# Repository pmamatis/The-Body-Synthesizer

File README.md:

Welcome to our lovely project. THE BODY-SYNTHESIZER. This is an educational project, which has been the topic of a course in digital signal processing and electronics at the Technical University Berlin, and is for non-commercial use only. The main goal of the project was to realize a digital audio-synthesizer, which can be controlled by various analog sensors. In case you wanna have a quick overview about the functionality, you can access the following YouTube-link: https://www.youtube.com/watch?v=VzIIO2eS0HQ&t=1586s

By: <br>
Maximillian Lehmer <br> Marc Bielen <br> Paul Mamatis

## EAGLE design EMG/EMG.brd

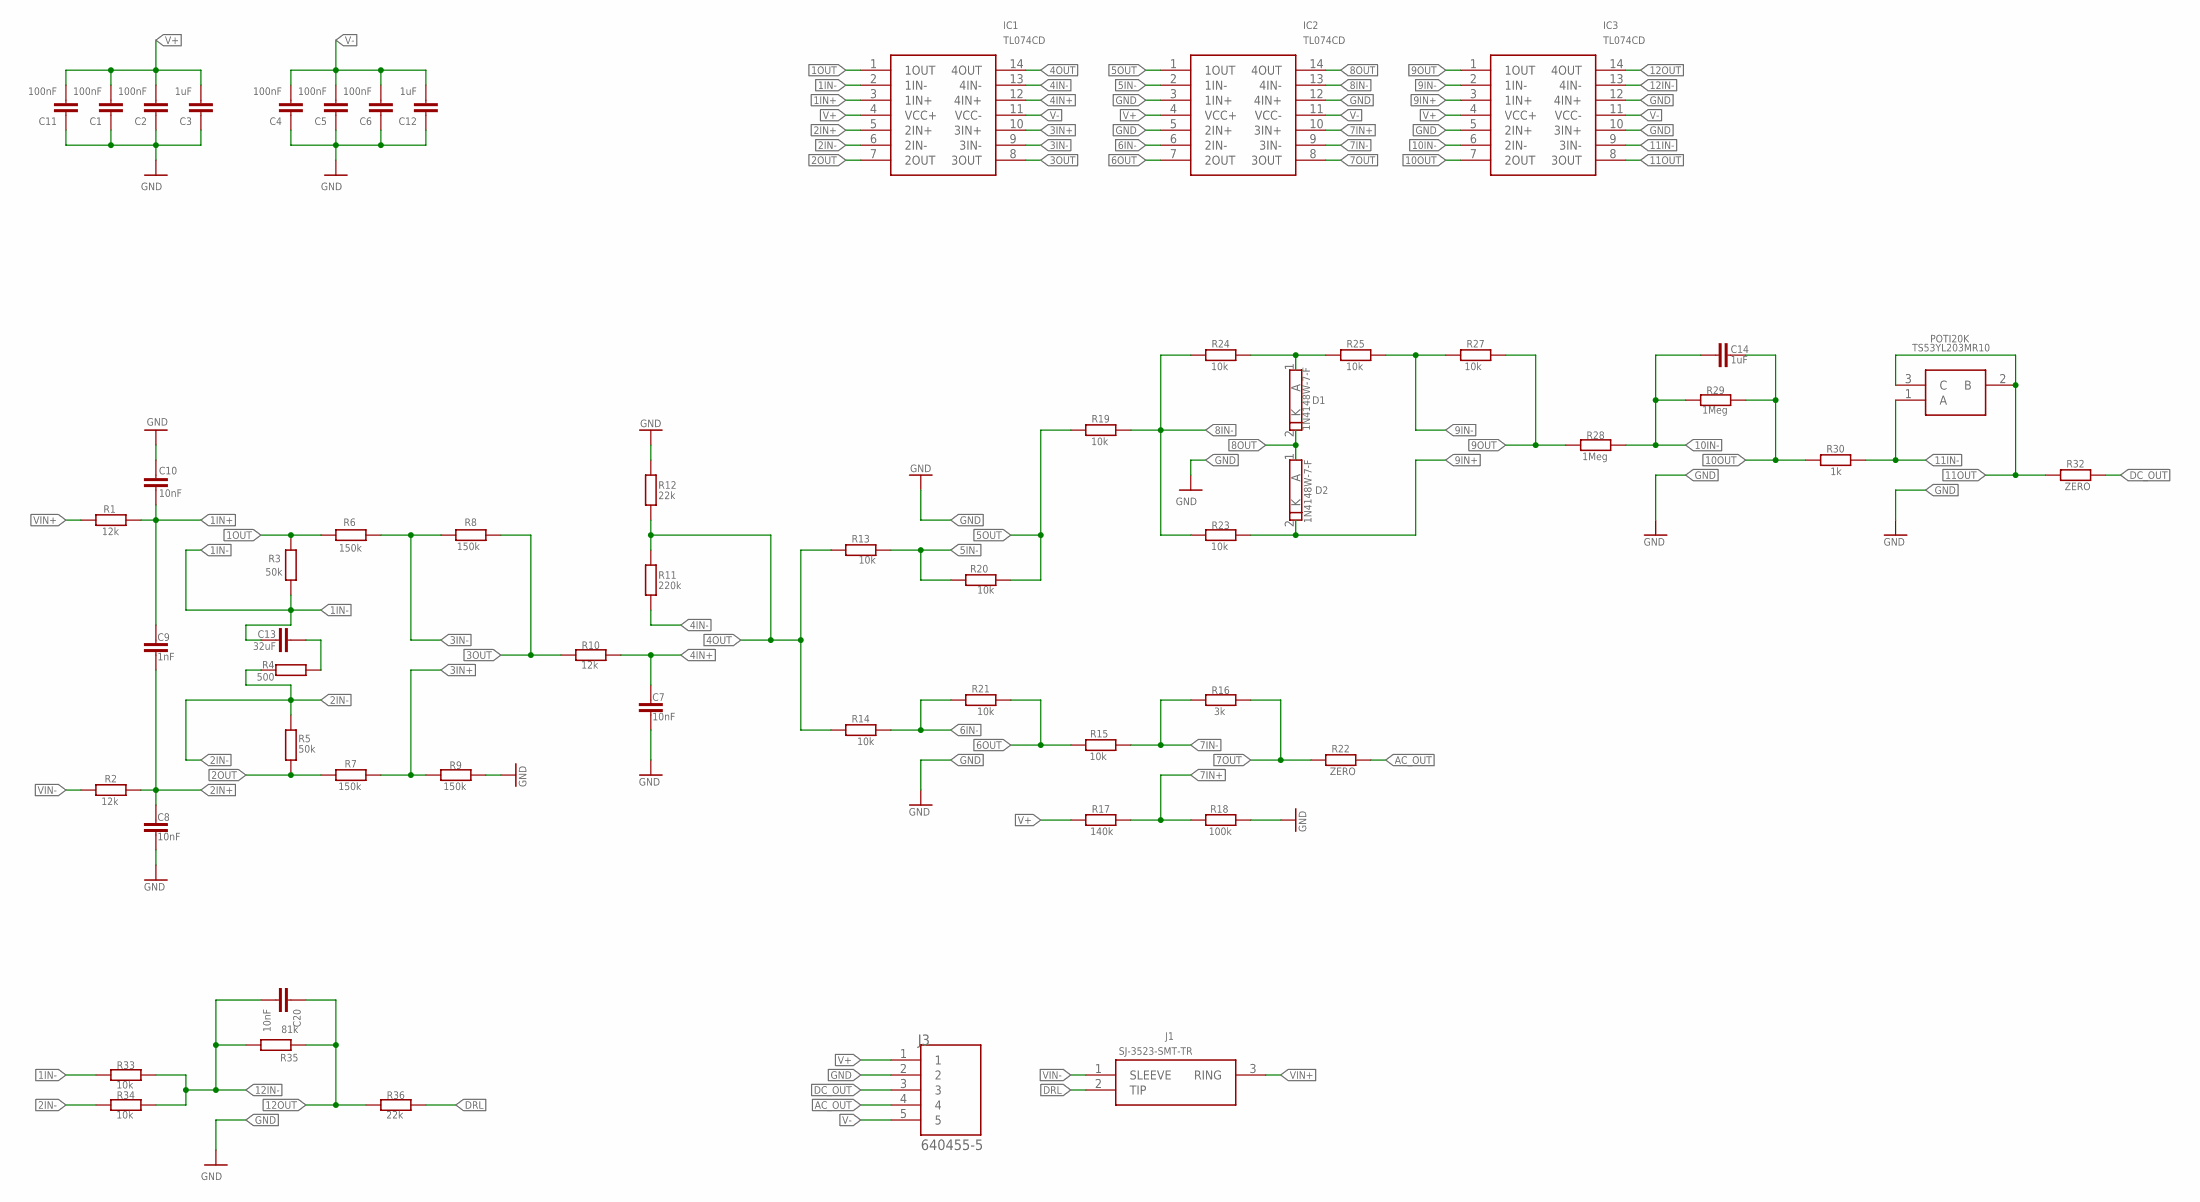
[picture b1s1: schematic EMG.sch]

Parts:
C1, C2, C4, C5, C6, C11: 100nF; C0603
C3, C12, C14: 1uF; C0603
C7, C8, C10, C20: 10nF; C0603
C9: 1nF; C0603
C13: 32uF; C0603
D1, D2: 1N4148W-7-F; SOD3716X115N
IC1, IC2, IC3: TL074CD; SOIC127P600X175-14N
J1: SJ-3523-SMT-TR; SJ3523SMTTR
J3: 640455-5; TE_640455-5
POTI20K: TS53YL203MR10
R1, R2, R10: 12k; R0603
R3, R5: 50k; R0603
R4: 500; R0603
R6, R7, R8, R9: 150k; R0603
R11: 220k; R0603
R12, R36: 22k; R0603
R13, R14, R15, R19, R20, R21, R23, R24, R25, R27, R33, R34: 10k; R0603
R16: 3k; R0603
R17: 140k; R0603
R18: 100k; R0603
R22, R32: ZERO; R0603
R28, R29: 1Meg; R0603
R30: 1k; R0603
R35: 81k; R0603

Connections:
1IN+: C9.1, C10.1, IC1.3 (1IN+), R1.2
1IN-: C13.1, IC1.2 (1IN-), R3.2, R33.2
1OUT: IC1.1 (1OUT), R3.1, R6.1
2IN+: C8.2, C9.2, IC1.5 (2IN+), R2.1
2IN-: IC1.6 (2IN-), R4.2, R5.1, R34.2
2OUT: IC1.7 (2OUT), R5.2, R7.2
3IN+: IC1.10 (3IN+), R7.1, R9.2
3IN-: IC1.9 (3IN-), R6.2, R8.2
3OUT: IC1.8 (3OUT), R8.1, R10.2
4IN+: C7.2, IC1.12 (4IN+), R10.1
4IN-: IC1.13 (4IN-), R11.2
4OUT: IC1.14 (4OUT), R11.1, R12.2, R13.2, R14.2
5IN-: IC2.2 (1IN-), R13.1, R20.2
5OUT: IC2.1 (1OUT), R19.2, R20.1
6IN-: IC2.6 (2IN-), R14.1, R21.2
6OUT: IC2.7 (2OUT), R15.2, R21.1
7IN+: IC2.10 (3IN+), R17.2, R18.1
7IN-: IC2.9 (3IN-), R15.1, R16.2
7OUT: IC2.8 (3OUT), R16.1, R22.2
8IN-: IC2.13 (4IN-), R19.1, R23.2, R24.2
8OUT: D1.2 (K), D2.1 (A), IC2.14 (4OUT)
9IN+: D2.2 (K), IC3.3 (1IN+), R23.1
9IN-: IC3.2 (1IN-), R25.1, R27.2
9OUT: IC3.1 (1OUT), R27.1, R28.2
10IN-: C14.1, IC3.6 (2IN-), R28.1, R29.2
10OUT: C14.2, IC3.7 (2OUT), R29.1, R30.2
11IN-: IC3.9 (3IN-), POTI20K.1 (A), R30.1
11OUT: IC3.8 (3OUT), POTI20K.2 (B), POTI20K.3 (C), R32.2
12IN-: C20.2, IC3.13 (4IN-), R33.1, R34.1, R35.2
12OUT: C20.1, IC3.14 (4OUT), R35.1, R36.2
AC_OUT: J3.4, R22.1
DC_OUT: J3.3, R32.1
DRL: J1.2 (TIP), R36.1
GND: C1.1, C2.1, C3.1, C4.1, C5.1, C6.1, C7.1, C8.1, C10.2, C11.1, C12.1, IC2.3 (1IN+), IC2.5 (2IN+), IC2.12 (4IN+), IC3.5 (2IN+), IC3.10 (3IN+), IC3.12 (4IN+), J3.2, R9.1, R12.1, R18.2
unnamed: D1.1 (A), R24.1, R25.2
unnamed: C13.2, R4.1
V+: C1.2, C2.2, C3.2, C11.2, IC1.4 (VCC+), IC2.4 (VCC+), IC3.4 (VCC+), J3.1, R17.1
V-: C4.2, C5.2, C6.2, C12.2, IC1.11 (VCC-), IC2.11 (VCC-), IC3.11 (VCC-), J3.5
VIN+: J1.3 (RING), R1.1
VIN-: J1.1 (SLEEVE), R2.2

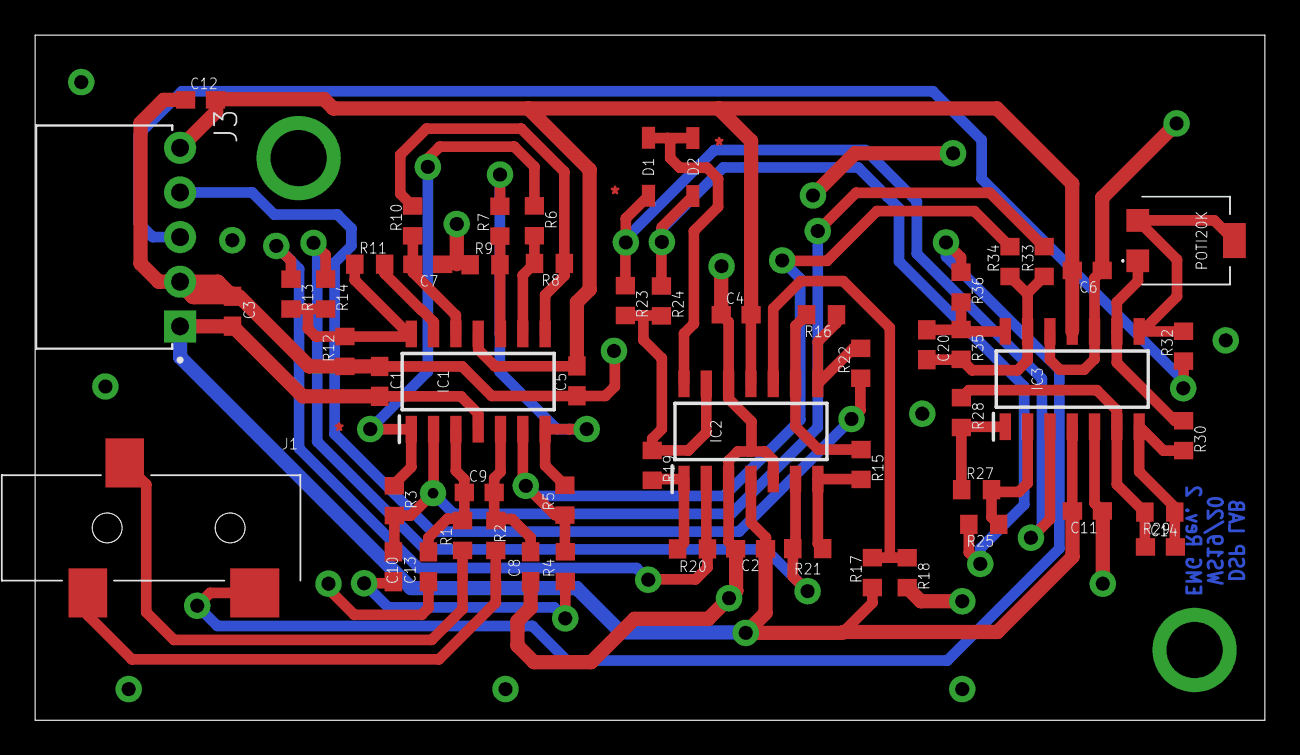
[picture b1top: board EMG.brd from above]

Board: 2 copper layers, 70.0 x 39.0 mm, 57 parts (0 on the bottom side), 40 nets.

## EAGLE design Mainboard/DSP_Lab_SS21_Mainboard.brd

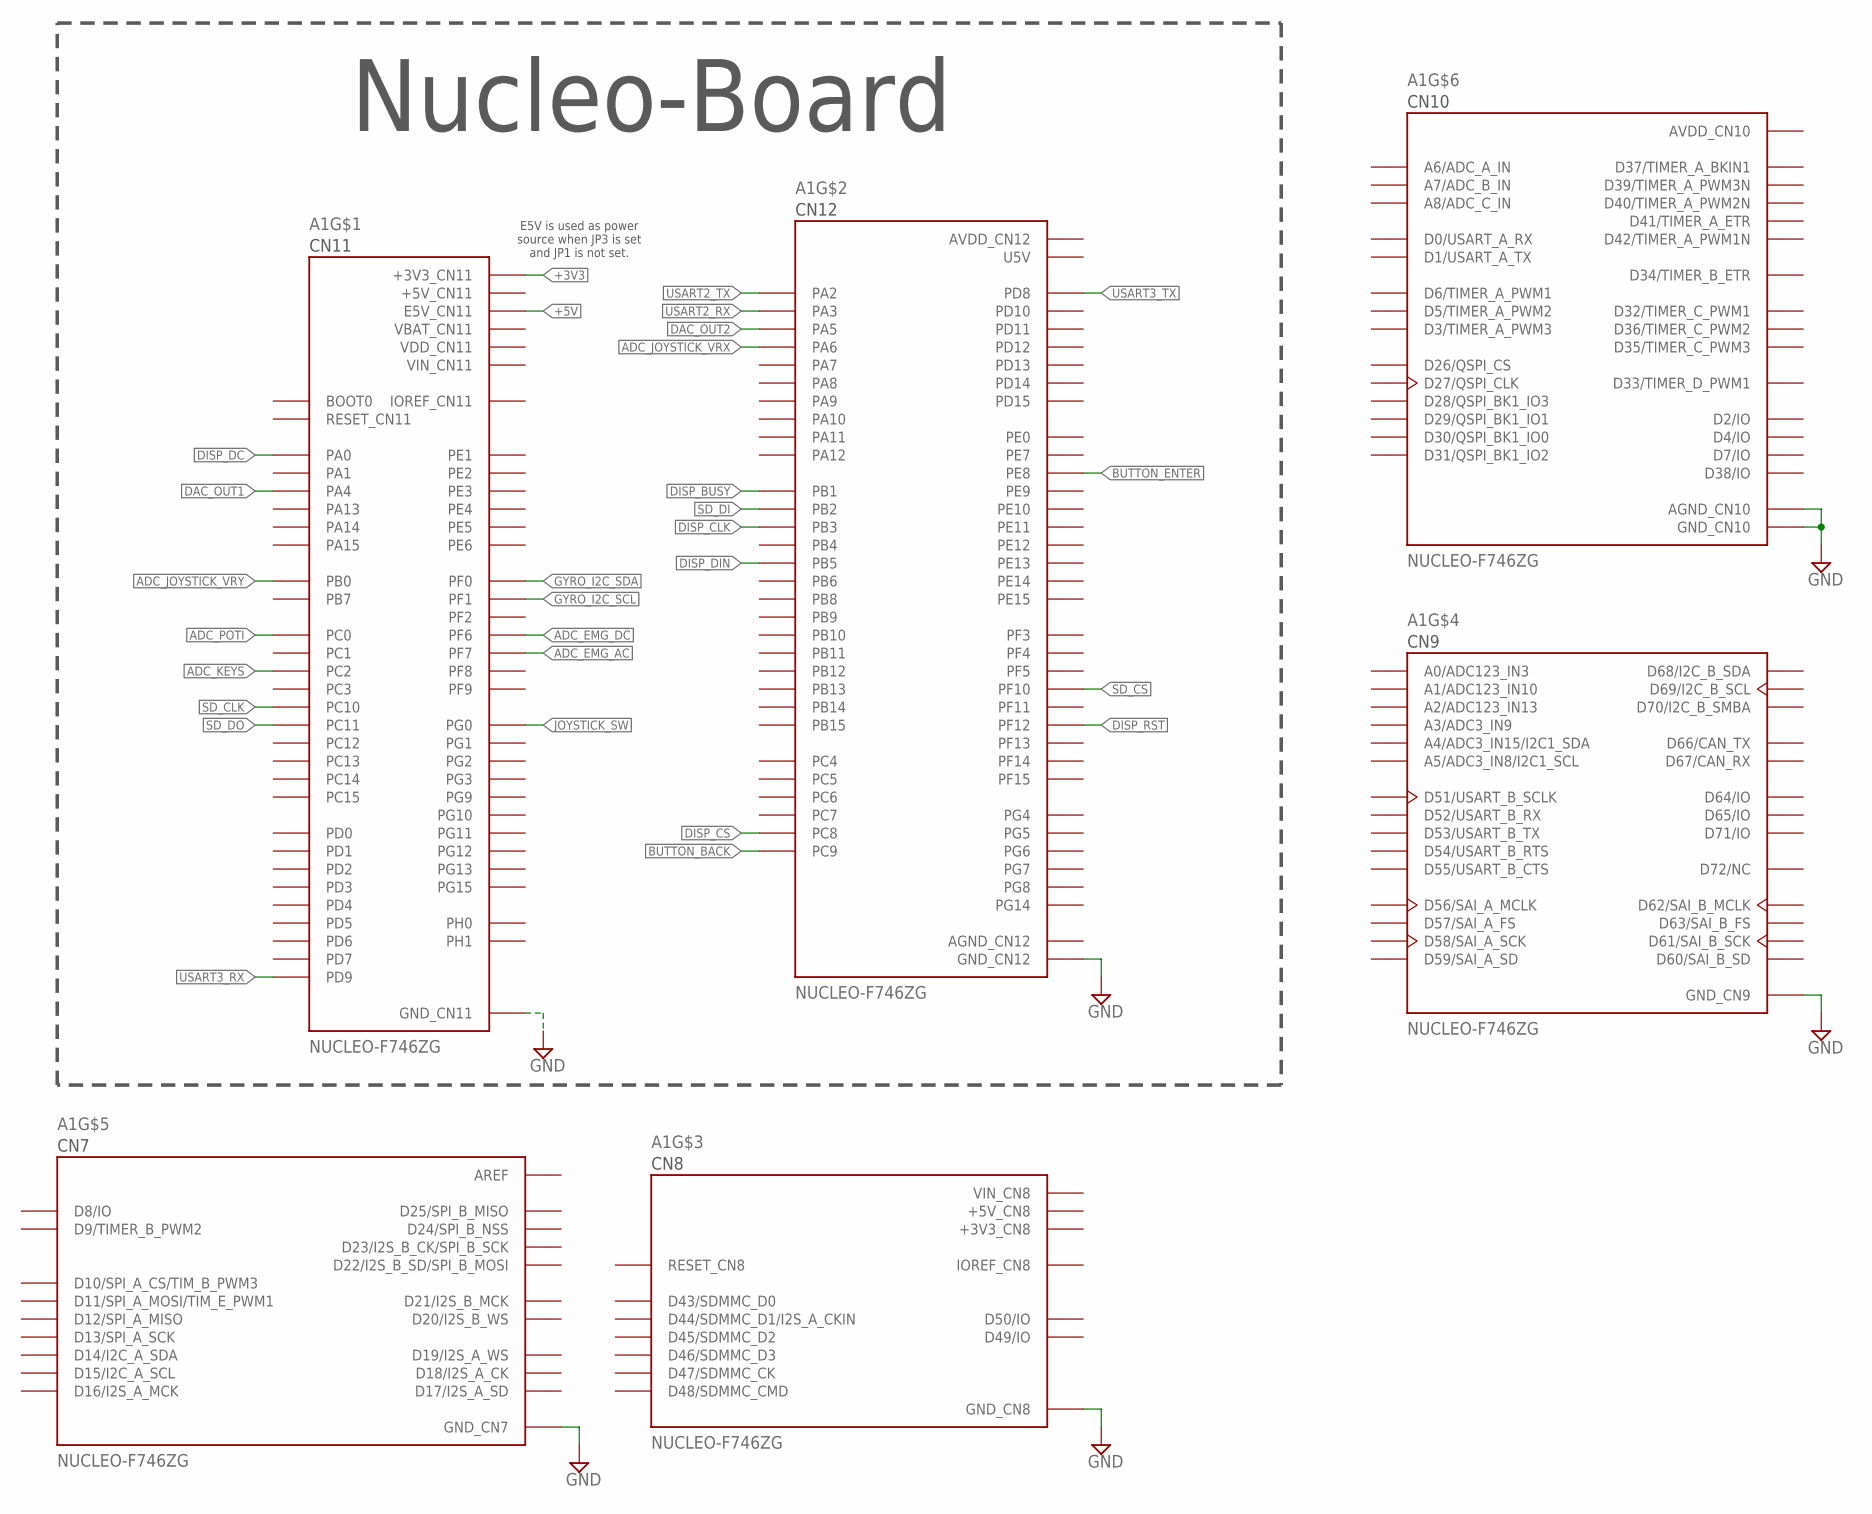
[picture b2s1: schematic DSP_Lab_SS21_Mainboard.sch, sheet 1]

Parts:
A1: NUCLEO-F746ZG; MODULE_NUCLEO-F746ZG

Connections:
+3V3: A1.CN11_16 (+3V3_CN11); also elsewhere on the board
+3V3_CN8: A1.CN8_7 (+3V3_CN8)
+5V: A1.CN11_6 (E5V_CN11); also elsewhere on the board
+5V_CN8: A1.CN8_9 (+5V_CN8)
+5V_CN11: A1.CN11_18 (+5V_CN11)
ADC_EMG_AC: A1.CN11_11 (PF7); also elsewhere on the board
ADC_EMG_DC: A1.CN11_9 (PF6); also elsewhere on the board
ADC_JOYSTICK_VRX: A1.CN12_13 (PA6); also elsewhere on the board
ADC_JOYSTICK_VRY: A1.CN11_34 (PB0); also elsewhere on the board
ADC_KEYS: A1.CN11_35 (PC2); also elsewhere on the board
ADC_POTI: A1.CN11_38 (PC0); also elsewhere on the board
AGND_CN12: A1.CN12_32 (AGND_CN12)
AREF: A1.CN7_6 (AREF)
AVDD_CN10: A1.CN10_1 (AVDD_CN10)
AVDD_CN12: A1.CN12_7 (AVDD_CN12)
BUTTON_BACK: A1.CN12_1 (PC9); also elsewhere on the board
BUTTON_ENTER: A1.CN12_40 (PE8); also elsewhere on the board
DAC_OUT1: A1.CN11_32 (PA4); also elsewhere on the board
DAC_OUT2: A1.CN12_11 (PA5); also elsewhere on the board
DISP_BUSY: A1.CN12_24 (PB1); also elsewhere on the board
DISP_CLK: A1.CN12_31 (PB3); also elsewhere on the board
DISP_CS: A1.CN12_2 (PC8); also elsewhere on the board
DISP_DC: A1.CN11_28 (PA0); also elsewhere on the board
DISP_DIN: A1.CN12_29 (PB5); also elsewhere on the board
DISP_RST: A1.CN12_59 (PF12); also elsewhere on the board
GND: A1.CN7_8 (GND_CN7), A1.CN8_11 (GND_CN8), A1.CN8_13 (GND_CN8), A1.CN9_12 (GND_CN9), A1.CN9_23 (GND_CN9), A1.CN10_3 (AGND_CN10), A1.CN10_5 (GND_CN10), A1.CN10_17 (GND_CN10), A1.CN10_22 (GND_CN10), A1.CN10_27 (GND_CN10), A1.CN11_8 (GND_CN11), A1.CN11_19 (GND_CN11), A1.CN11_20 (GND_CN11), A1.CN11_22 (GND_CN11), A1.CN11_49 (GND_CN11), A1.CN11_60 (GND_CN11), A1.CN11_71 (GND_CN11), A1.CN11_72 (GND_CN11), A1.CN12_9 (GND_CN12), A1.CN12_20 (GND_CN12), A1.CN12_39 (GND_CN12), A1.CN12_54 (GND_CN12), A1.CN12_63 (GND_CN12), A1.CN12_71 (GND_CN12), A1.CN12_72 (GND_CN12); also elsewhere on the board
GYRO_I2C_SCL: A1.CN11_51 (PF1); also elsewhere on the board
GYRO_I2C_SDA: A1.CN11_53 (PF0); also elsewhere on the board
JOYSTICK_SW: A1.CN11_59 (PG0); also elsewhere on the board
SD_CLK: A1.CN11_1 (PC10); also elsewhere on the board
SD_CS: A1.CN12_42 (PF10); also elsewhere on the board
SD_DI: A1.CN12_22 (PB2); also elsewhere on the board
SD_DO: A1.CN11_2 (PC11); also elsewhere on the board
U5V: A1.CN12_8 (U5V)
USART2_RX: A1.CN12_37 (PA3)
USART2_TX: A1.CN12_35 (PA2)
USART3_RX: A1.CN11_69 (PD9)
USART3_TX: A1.CN12_10 (PD8)
VBAT_CN11: A1.CN11_33 (VBAT_CN11)
VDD_CN11: A1.CN11_5 (VDD_CN11)
VIN_CN8: A1.CN8_15 (VIN_CN8)
VIN_CN11: A1.CN11_24 (VIN_CN11)

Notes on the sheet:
Nucleo-Board
E5V is used as power source when JP3 is set and JP1 is not set.

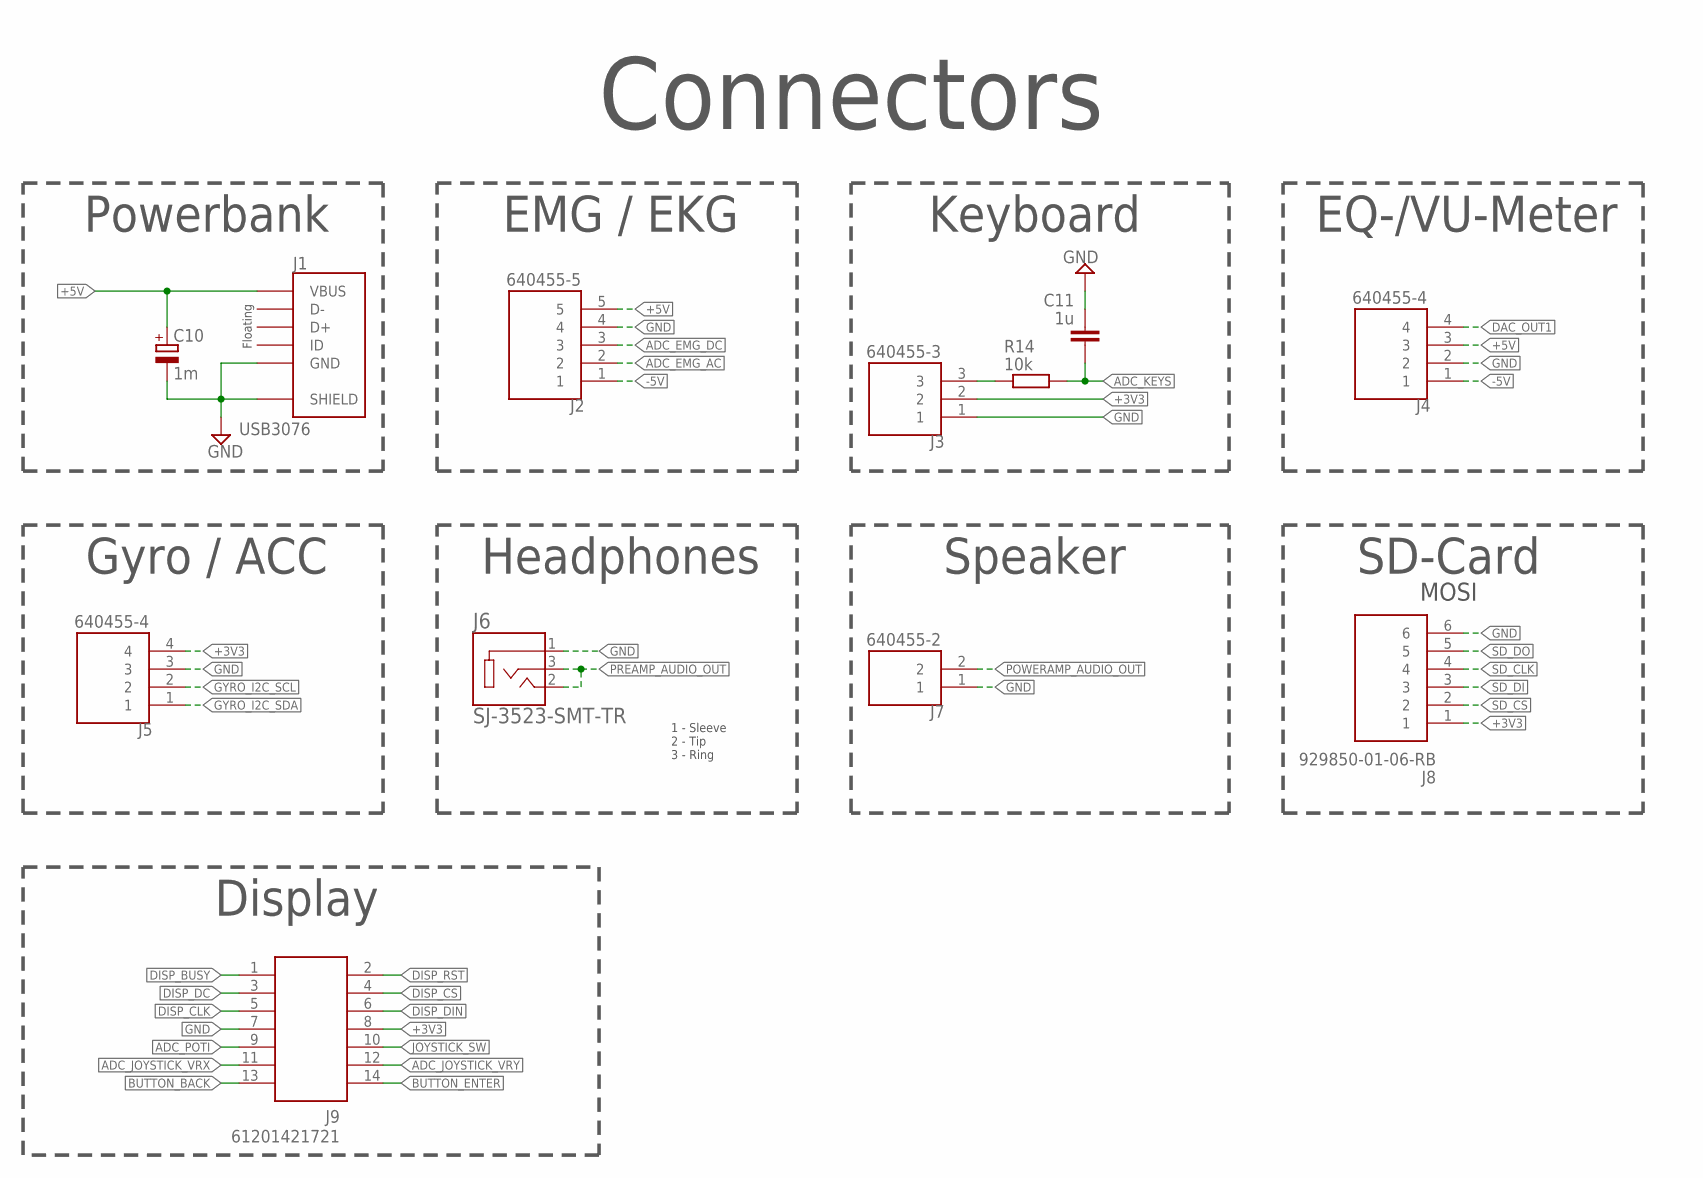
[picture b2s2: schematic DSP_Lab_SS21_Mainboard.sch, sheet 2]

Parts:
C10: 1m; E2,5-5
C11: 1u; C0603
J1: USB3076; GCT_USB3076-XX-X_REVC
J2: 640455-5; TE_640455-5
J3: 640455-3; TE_640455-3
J4, J5: 640455-4; TE_640455-4
J6: SJ-3523-SMT-TR; CUI_SJ-3523-SMT-TR
J7: 640455-2; TE_640455-2
J8: 929850-01-06-RB; RHDR6W76P0X254_1X6_1524X254X82
J9: 61201421721
R14: 10k; R0603

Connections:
+3V3: J3.2, J5.4, J8.1, J9.8; also elsewhere on the board
+5V: C10.+, J1.1 (VBUS), J2.5, J4.3; also elsewhere on the board
-5V: J2.1, J4.1; also elsewhere on the board
ADC_EMG_AC: J2.2; also elsewhere on the board
ADC_EMG_DC: J2.3; also elsewhere on the board
ADC_JOYSTICK_VRX: J9.11; also elsewhere on the board
ADC_JOYSTICK_VRY: J9.12; also elsewhere on the board
ADC_KEYS: C11.1, R14.2; also elsewhere on the board
ADC_POTI: J9.9; also elsewhere on the board
BUTTON_BACK: J9.13; also elsewhere on the board
BUTTON_ENTER: J9.14; also elsewhere on the board
DAC_OUT1: J4.4; also elsewhere on the board
DISP_BUSY: J9.1; also elsewhere on the board
DISP_CLK: J9.5; also elsewhere on the board
DISP_CS: J9.4; also elsewhere on the board
DISP_DC: J9.3; also elsewhere on the board
DISP_DIN: J9.6; also elsewhere on the board
DISP_RST: J9.2; also elsewhere on the board
GND: C10.-, C11.2, J1.5 (GND), J1.6 (SHIELD), J1.7 (SHIELD), J1.8 (SHIELD), J1.9 (SHIELD), J1.10 (SHIELD), J1.11 (SHIELD), J2.4, J3.1, J4.2, J5.3, J6.1, J7.1, J8.6, J9.7; also elsewhere on the board
GYRO_I2C_SCL: J5.2; also elsewhere on the board
GYRO_I2C_SDA: J5.1; also elsewhere on the board
JOYSTICK_SW: J9.10; also elsewhere on the board
unnamed: J3.3, R14.1
POWERAMP_AUDIO_OUT: J7.2; also elsewhere on the board
PREAMP_AUDIO_OUT: J6.2, J6.3; also elsewhere on the board
SD_CLK: J8.4; also elsewhere on the board
SD_CS: J8.2; also elsewhere on the board
SD_DI: J8.3; also elsewhere on the board
SD_DO: J8.5; also elsewhere on the board

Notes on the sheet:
Floating
Connectors
Powerbank
Display
EMG / EKG
Keyboard
EQ-/VU-Meter
Gyro / ACC
Headphones
Speaker
SD-Card
1 - Sleeve 2 - Tip 3 - Ring
MOSI

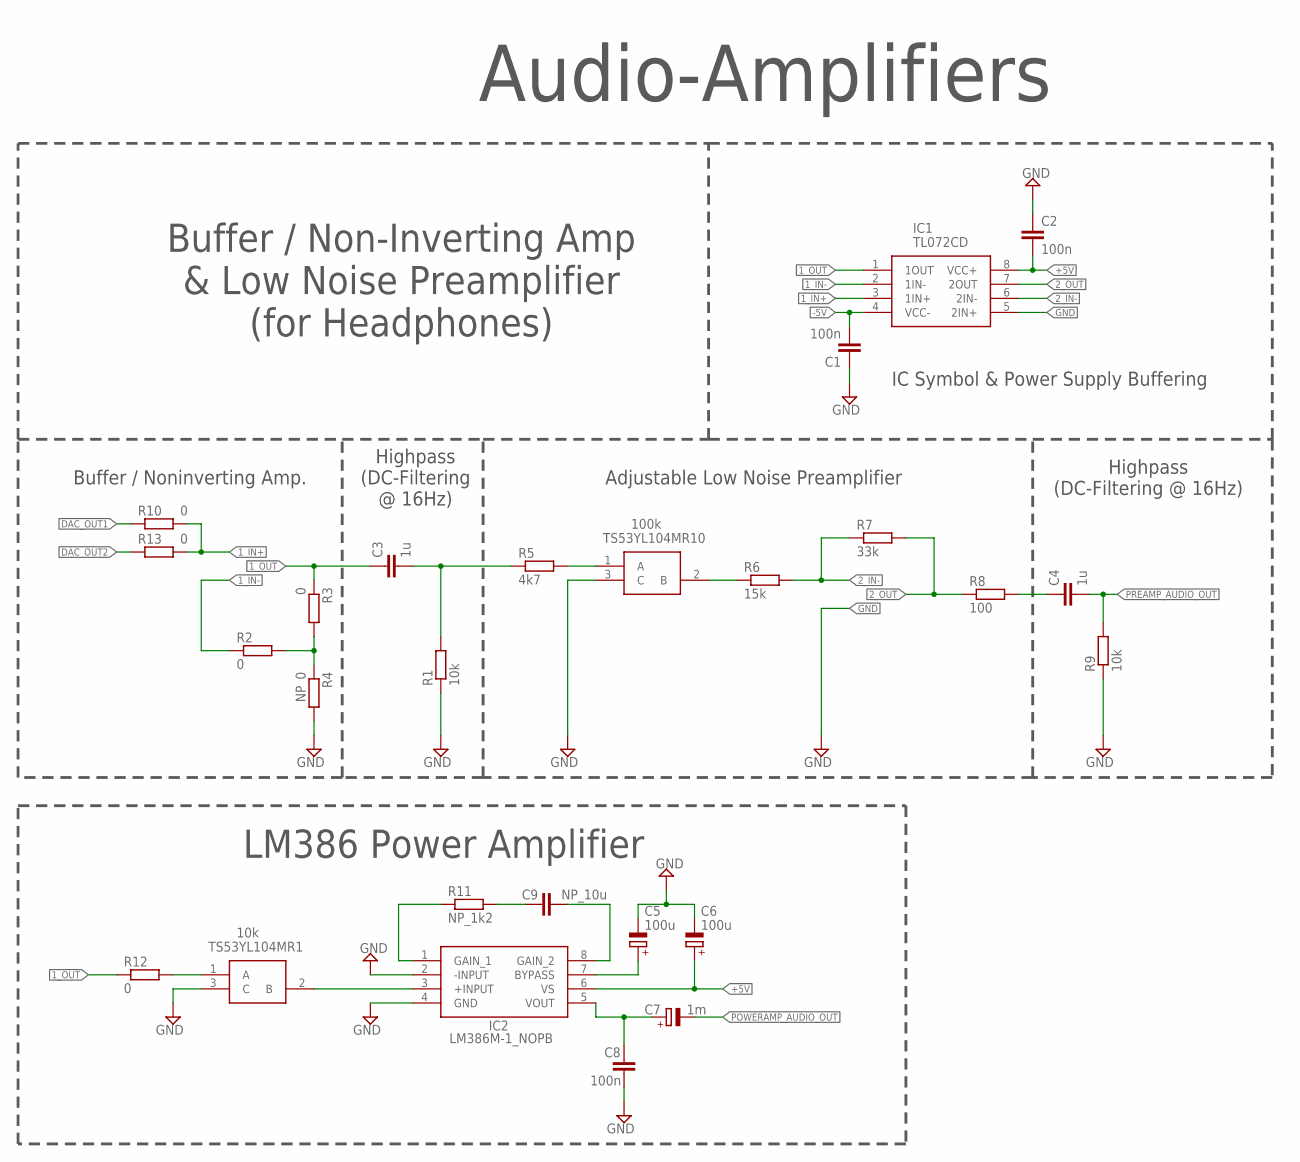
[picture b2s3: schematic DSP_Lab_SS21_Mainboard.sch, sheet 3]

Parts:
C1, C2, C8: 100n; C0603
C3, C4: 1u; C0603
C5, C6: 100u; E2,5-5
C7: 1m; E2,5-5
C9: NP_10u; C0603
IC1: TL072CD; SOIC127P600X175-8N
IC2: LM386M-1_NOPB; SOIC127P600X175-8N
R1, R9: 10k; R0603
R2, R3, R10, R12, R13: 0; R0603
R4: NP_0; R0603
R5: 4k7; R0603
R6: 15k; R0603
R7: 33k; R0603
R8: 100; R0603
R11: NP_1k2; R0603
TS53YL104MR1: 10k; TS53YL203MR10
TS53YL104MR10: 100k; TS53YL203MR10

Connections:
1_IN+: IC1.3 (1IN+), R10.2, R13.2
1_IN-: IC1.2 (1IN-), R2.1
1_OUT: C3.1, IC1.1 (1OUT), R3.1, R12.1
2_IN-: IC1.6 (2IN-), R6.2, R7.1
2_OUT: IC1.7 (2OUT), R7.2, R8.1
+5V: C2.2, C6.+, IC1.8 (VCC+), IC2.6 (VS); also elsewhere on the board
-5V: C1.2, IC1.4 (VCC-); also elsewhere on the board
DAC_OUT1: R10.1; also elsewhere on the board
DAC_OUT2: R13.1; also elsewhere on the board
GND: C1.1, C2.1, C5.-, C6.-, C8.2, IC1.5 (2IN+), IC2.2 (-INPUT), IC2.4 (GND), R1.1, R4.2, R9.1, TS53YL104MR1.3 (C), TS53YL104MR10.3 (C); also elsewhere on the board
unnamed: C3.2, R1.2, R5.1
unnamed: R2.2, R3.2, R4.1
unnamed: R5.2, TS53YL104MR10.1 (A)
unnamed: R6.1, TS53YL104MR10.2 (B)
unnamed: C4.1, R8.2
unnamed: IC2.1 (GAIN_1), R11.1
unnamed: IC2.3 (+INPUT), TS53YL104MR1.2 (B)
unnamed: C9.1, R11.2
unnamed: C9.2, IC2.8 (GAIN_2)
unnamed: R12.2, TS53YL104MR1.1 (A)
unnamed: C5.+, IC2.7 (BYPASS)
unnamed: C7.+, C8.1, IC2.5 (VOUT)
POWERAMP_AUDIO_OUT: C7.-; also elsewhere on the board
PREAMP_AUDIO_OUT: C4.2, R9.2; also elsewhere on the board

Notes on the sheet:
Audio-Amplifiers
Buffer / Non-Inverting Amp & Low Noise Preamplifier (for Headphones)
Highpass (DC-Filtering @ 16Hz)
Highpass (DC-Filtering @ 16Hz)
Buffer / Noninverting Amp.
Adjustable Low Noise Preamplifier
IC Symbol & Power Supply Buffering
LM386 Power Amplifier

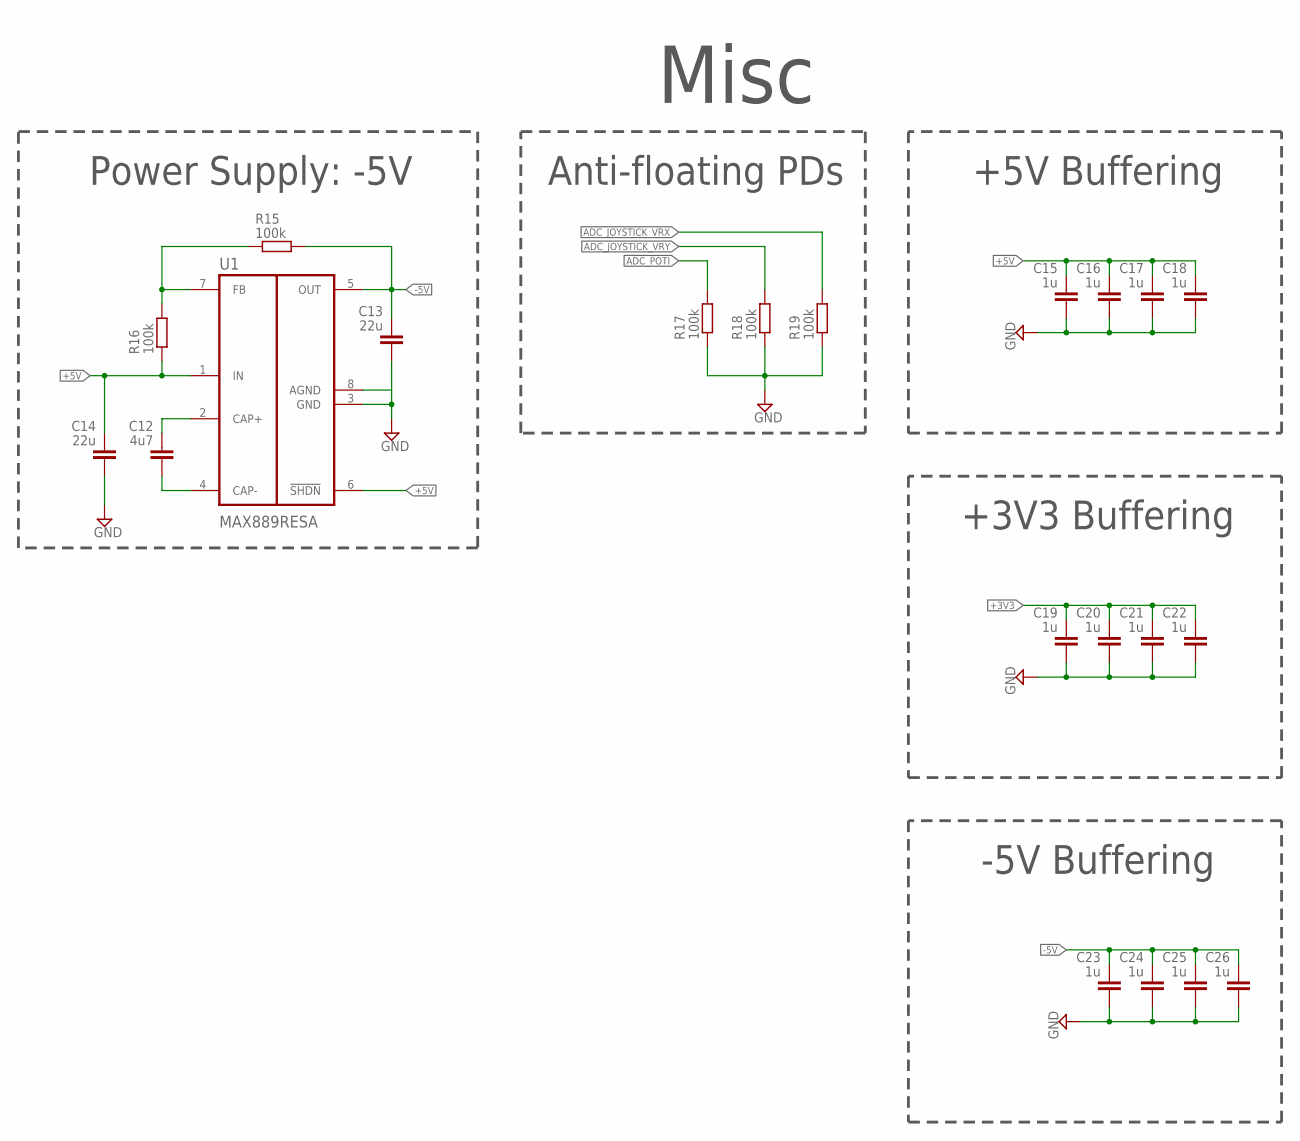
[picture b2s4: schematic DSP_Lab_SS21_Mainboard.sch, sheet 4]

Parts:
C12: 4u7; C0603
C13, C14: 22u; C0603
C15, C16, C17, C18, C19, C20, C21, C22, C23, C24, C25, C26: 1u; C0603
R15, R16, R17, R18, R19: 100k; R0603
U1: MAX889RESA; SOIC127P600X175-8N

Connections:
+3V3: C19.2, C20.2, C21.2, C22.2; also elsewhere on the board
+5V: C14.2, C15.2, C16.2, C17.2, C18.2, R16.1, U1.1 (IN), U1.6 (!SHDN); also elsewhere on the board
-5V: C13.2, C23.2, C24.2, C25.2, C26.2, R15.2, U1.5 (OUT); also elsewhere on the board
ADC_JOYSTICK_VRX: R19.2; also elsewhere on the board
ADC_JOYSTICK_VRY: R18.2; also elsewhere on the board
ADC_POTI: R17.2; also elsewhere on the board
GND: C13.1, C14.1, C15.1, C16.1, C17.1, C18.1, C19.1, C20.1, C21.1, C22.1, C23.1, C24.1, C25.1, C26.1, R17.1, R18.1, R19.1, U1.3 (GND), U1.8 (AGND); also elsewhere on the board
unnamed: R15.1, R16.2, U1.7 (FB)
unnamed: C12.2, U1.2 (CAP+)
unnamed: C12.1, U1.4 (CAP-)

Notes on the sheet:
Anti-floating PDs
Misc
Power Supply: -5V
+5V Buffering
+3V3 Buffering
-5V Buffering

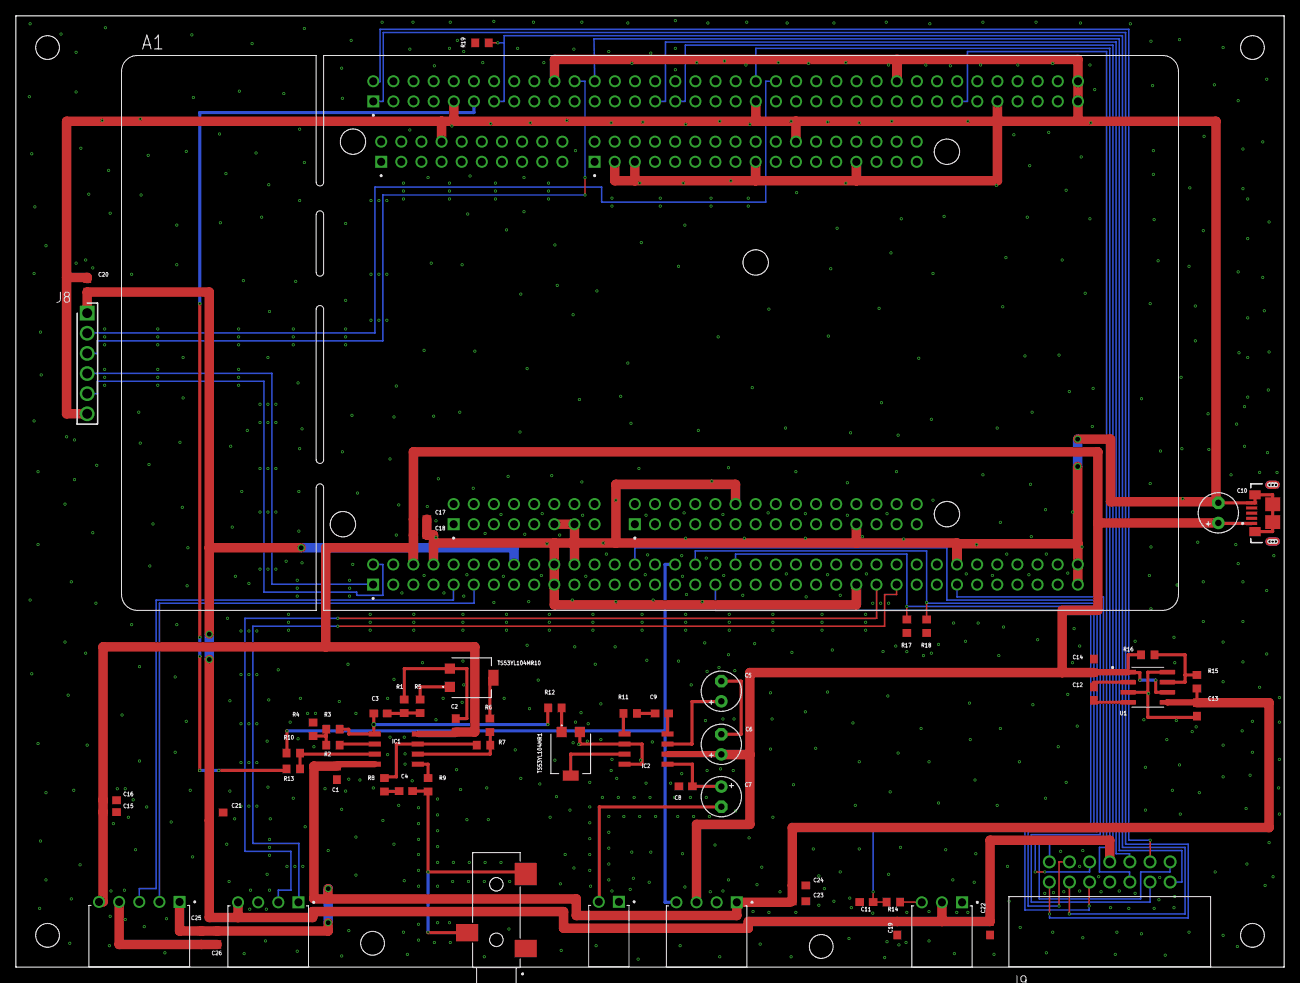
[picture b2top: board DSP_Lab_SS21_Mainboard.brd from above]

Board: 2 copper layers, 160.0 x 120.0 mm, 60 parts (0 on the bottom side), 50 nets.

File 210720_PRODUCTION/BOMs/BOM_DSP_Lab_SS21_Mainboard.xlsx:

Qty | Value | Device | Package | Parts | Description | AVAILABILITY | COMMENT | CUI_PURCHASE_URL | DESCRIPTION | DIGI-KEY_PART_NUMBER | DIGI-KEY_PURCHASE_URL | EU_ROHS_COMPLIANCE | HEIGHT | MANUFACTURER_NAME | MANUFACTURER_PART_NUMBER | MF | MOUSER_PART_NUMBER | MOUSER_PRICE-STOCK | MP | PACKAGE | PRICE | PURCHASE-URL | TE_PURCHASE_URL
5 | 0 | R-EU_R0603 | R0603 | R2, R3, R10, R12, R13 | RESISTOR, European symbol
1 | 100 | R-EU_R0603 | R0603 | R8 | RESISTOR, European symbol
2 | 100k | R-EU_R0603 | R0603 | R15, R16 | RESISTOR, European symbol
1 | 100k | TS53YL203MR10 | TS53YL203MR10 | TS53YL104MR10 | Vishay TS53YL Series SMD Trimmer Resistor with Gull Wing Terminations, 20k +/-2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 |  |  |  | Vishay TS53YL Series SMD Trimmer Resistor with Gull Wing Terminations, 20k +/-2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 |  |  |  | 2.7mm | Vishay | TS53YL203MR10 |  | 72-TS53YL-20K | https://www.mouser.com/Search/Refine.aspx?Keyword=72-TS53YL-20K
3 | 100n | C-EUC0603 | C0603 | C1, C2, C8 | CAPACITOR, European symbol
2 | 100u | CPOL-EUE2.5-5 | E2,5-5 | C5, C6 | POLARIZED CAPACITOR, European symbol
3 | 10k | R-EU_R0603 | R0603 | R1, R9, R14 | RESISTOR, European symbol
1 | 10k | TS53YL203MR10 | TS53YL203MR10 | TS53YL104MR1 | Vishay TS53YL Series SMD Trimmer Resistor with Gull Wing Terminations, 20k +/-2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 |  |  |  | Vishay TS53YL Series SMD Trimmer Resistor with Gull Wing Terminations, 20k +/-2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 |  |  |  | 2.7mm | Vishay | TS53YL203MR10 |  | 72-TS53YL-20K | https://www.mouser.com/Search/Refine.aspx?Keyword=72-TS53YL-20K
1 | 15k | R-EU_R0603 | R0603 | R6 | RESISTOR, European symbol
3 | 1Meg | R-EU_R0603 | R0603 | R17, R18, R19 | RESISTOR, European symbol
2 | 1m | CPOL-EUE2.5-5 | E2,5-5 | C7, C10 | POLARIZED CAPACITOR, European symbol
15 | 1u | C-EUC0603 | C0603 | C3, C4, C11, C15, C16, C17, C18, C19, C20, C21, C22, C23, C24, C25, C26 | CAPACITOR, European symbol
2 | 22u | C-EUC0603 | C0603 | C13, C14 | CAPACITOR, European symbol
1 | 33k | R-EU_R0603 | R0603 | R7 | RESISTOR, European symbol
1 | 4k7 | R-EU_R0603 | R0603 | R5 | RESISTOR, European symbol
1 | 4u7 | C-EUC0603 | C0603 | C12 | CAPACITOR, European symbol
1 | 61201421721 | 61201421721 | 61201421721 | J9 | WR-BHD 2.54mm Male Angled Box Header, 14 Pins=>Code : Con_WTB_BHD_2.54_Male_THT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 | In Stock |  |  | Connector Header Through Hole, Right Angle 14 position 0.100 (2.54mm) |  |  |  |  |  |  | Würth Elektronik |  |  | 61201421721 | None | None
1 | 640455-2 | 640455-2 | TE_640455-2 | J7 | Check prices | In Stock | 640455-2 |  | MTA-100 2 Position 2.54 mm Single Row Right Angle Wire to Board Header |  |  | Compliant |  |  |  | TE Connectivity |  |  | 640455-2 | None | None | https://pricing.snapeda.com/search/part/640455-2/?ref=eda
1 | 640455-3 | 640455-3 | TE_640455-3 | J3 | Check prices | In Stock | 640455-3 |  | Connector Header Through Hole, Right Angle 3 position 0.100 (2.54mm) |  |  | Compliant |  |  |  | TE Connectivity |  |  | 640455-3 | None | None | https://pricing.snapeda.com/search/part/640455-3/?ref=eda
2 | 640455-4 | 640455-4 | TE_640455-4 | J4, J5 | Check prices | In Stock | 640455-4 |  | Headers & Receptacles cable a placa 8 POS MONO SHAPE MKII TAB ASS'Y GW 750.N TY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 |  |  | Compliant |  |  |  | TE Connectivity |  |  | 640455-4 | None | None
1 | 640455-5 | 640455-5 | TE_640455-5 | J2 |  |  | 640455-5 |  | MTA-100 5 Position Through Hole Single Row Right Angle Wire to Board Header | A19453-ND | https://www.digikey.de/product-detail/en/te-connectivity-amp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 |  |  |  |  | TE Connectivity |  |  | 640455-5 | None |  |  | https://www.te.com/usa-en/product-640455-5.html?te_bu=Cor&te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
1 | 929850-01-06-RB | 929850-01-06-RB | RHDR6W76P0X254_1X6_1524X254X82 | J8 | Headers & Wire Housings 6P STRT BRD MNT SKT 1 ROW 30MICRO AU" |  |  |  | Headers & Wire Housings 6P STRT BRD MNT SKT 1 ROW 30MICRO AU" |  |  |  | 8.26mm | 3M | 929850-01-06-RB |  | 517-929850-01-06-RB | https://www.mouser.co.uk/ProductDetail/3M-Electronic-Solutio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
1 | LM386M-1_NOPB | LM386M-1_NOPB | SOIC127P600X175-8N | IC2 | Wide Input Voltage Low Power Audio Amplifier with Internal Gain |  |  |  | Wide Input Voltage Low Power Audio Amplifier with Internal Gain |  |  |  | 1.75mm | Texas Instruments | LM386M-1/NOPB |  | 926-LM386M-1/NOPB | https://www.mouser.co.uk/ProductDetail/Texas-Instruments/LM3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
1 | MAX889RESA | MAX889RESA | SOIC127P600X175-8N | U1 | Check prices | In Stock |  |  | Charge Pump Switching Regulator IC Negative Adjustable -2.5V 1 Output 200mA 8-S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 |  |  |  |  |  |  | Maxim Integrated |  |  | MAX889RESA+ | SOIC-8 Maxim | None
1 | NP_0 | R-EU_R0603 | R0603 | R4 | RESISTOR, European symbol
1 | NP_10u | C-EUC0603 | C0603 | C9 | CAPACITOR, European symbol
1 | NP_1k2 | R-EU_R0603 | R0603 | R11 | RESISTOR, European symbol
1 | NUCLEO-F746ZG | NUCLEO-F746ZG | MODULE_NUCLEO-F746ZG | A1 | STM32 Nucleo-144 development board with STM32F746ZG MCU, supports Arduino, ST Z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 | In Stock |  |  | STM32F746ZG, mbed-Enabled Development Nucleo-144 STM32F7 ARM® Cortex®-M7 MCU 32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 |  |  |  |  |  |  | STMicroelectronics |  |  | NUCLEO-F746ZG | None | None
1 | SJ-3523-SMT-TR | SJ-3523-SMT-TR | CUI_SJ-3523-SMT-TR | J6 | Audio Jack Connector 3.5 mm Low Profile Surface Mount Stereo Jack, 3 Pin Right-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 | In Stock |  | https://www.cuidevices.com/product/interconnect/connectors/a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 | 3.5 mm, Stereo, Right Angle, Surface Mount (SMT), 3 Conductors, 0~1 Internal Sw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 |  |  |  |  |  |  | CUI Devices |  |  | SJ-3523-SMT-TR | LGA-10 STMicroelectronics | None
1 | TL072CD | TL072CD | SOIC127P600X175-8N | IC1 | Dual Low-Noise JFET-Input General-Purpose Operational Amplifier |  |  |  | Dual Low-Noise JFET-Input General-Purpose Operational Amplifier |  |  |  | 1.75mm | Texas Instruments | TL072CD |  | 595-TL072CD | https://www.mouser.com/Search/Refine.aspx?Keyword=595-TL072CD
1 | USB3076 | USB3076-XX-X_REVC | GCT_USB3076-XX-X_REVC | J1 | Micro USB Receptacle, Type B, SMT, Horizontal, Bottom Mount w/out Peg, w/out Sh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 | In Stock |  |  | USB - micro B USB 2.0 Receptacle Connector 5 Position Surface Mount, Right Angle | Through Hole, 2.35mm profile, 5 Pins, Horizontal, Bottom mount |  |  |  |  |  |  | Global Connector Technology |  |  | USB3076-30-A | None | None

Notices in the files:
Core/Inc/display.h:
@copyright Copyright (c) 2022
parts and their libraries:
SparkFun-Resistors: Licensing: Creative Commons ShareAlike 4.0 International - https://creativecommons.org/licenses/by-sa/4.0
